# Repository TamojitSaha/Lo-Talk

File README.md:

<h1 align="center">Lo-Talk</h1>

# About

Lo-Talk is an open-hardware ISM band off-grid communicator based on Nordic's NRF51822 and Semtech's LoRa module on SX1278. This device can be helpful in node to node communication and mesh networking over the ISM band and has hardware support for SOS alerts.
The device communication range was tested upto 500mm in an urban area without line of sight and maximum Tx Power 0.3W.

# Schematic

# Layout

# License
The source files are released under  [Creative Commons Attribution-NonCommercial-NoDerivatives 4.0 International License](http://creativecommons.org/licenses/by-nc-nd/4.0/) .

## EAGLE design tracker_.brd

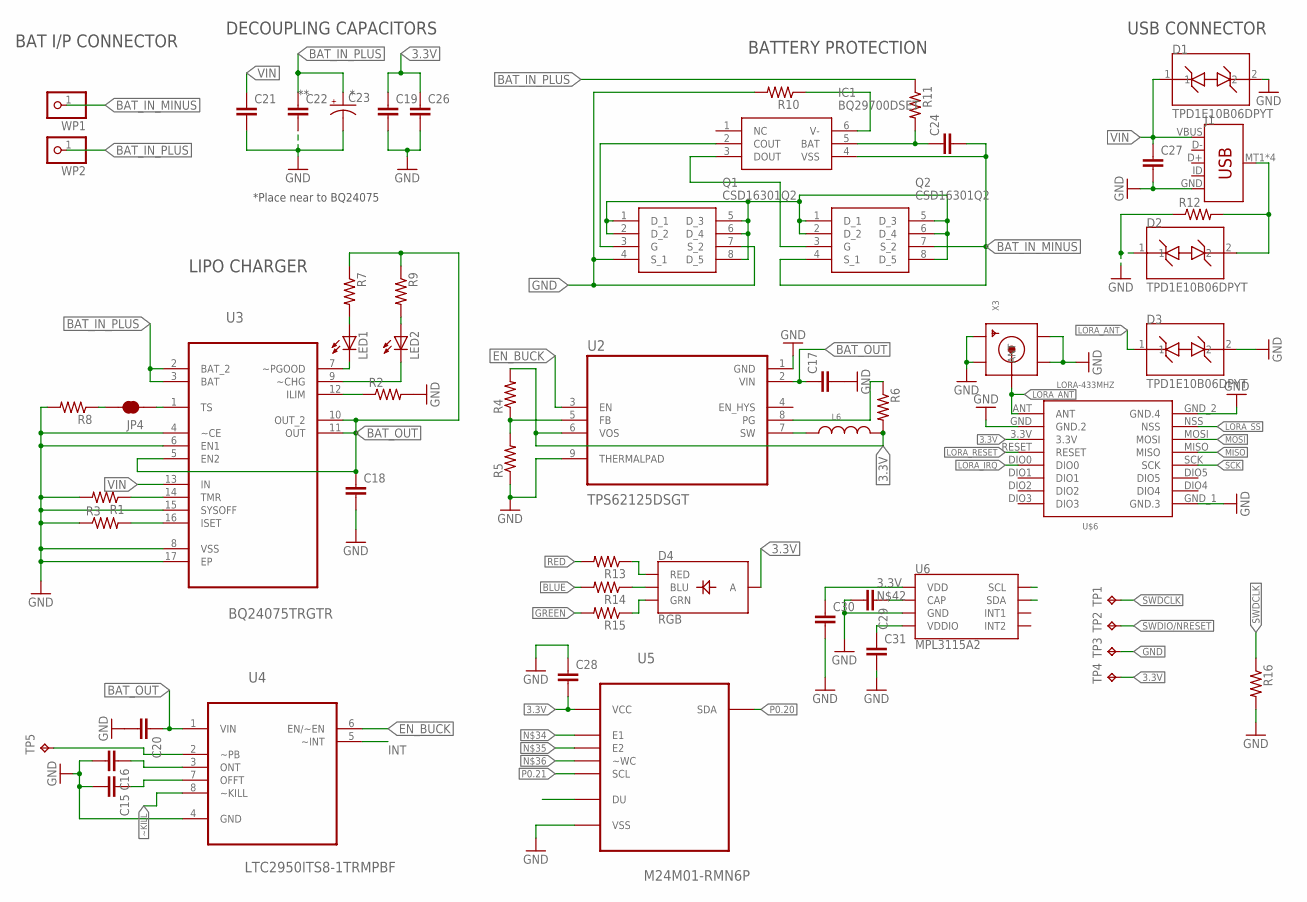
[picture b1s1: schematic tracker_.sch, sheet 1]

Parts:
C15, C16, C17, C18, C20, C21, C28, C29, C30, C31: C-EUC0402; C0402
C19, C24, C26, C27: C-EUC0603; C0603
C22: C-EUC0805K; C0805K
C23: CPOL-USB/3528-21W; B/3528-21W
D1, D2, D3: TPD1E10B06DPYT; DFN100X60X45-2N
D4: RGB; P-LCC-4-3
IC1: BQ29700DSET; SON50P150X150X80-6N
J1: USB_MICRO-B_SMT; USB-MICROB
JP4: JUMPER-SMT_2_NC_TRACE_SILK; SMT-JUMPER_2_NC_TRACE_SILK
L6: WE-GF_1210(M)_744764115; WE-GF_1210
LED1, LED2: LEDCHIPLED_0603; CHIPLED_0603
Q1, Q2: CSD16301Q2
R1, R2, R3, R4, R5, R6, R7, R8, R9, R10, R12, R13, R14, R15, R16: R-US_R0402; R0402
R11: R-US_M0805; M0805
TP1, TP2, TP3, TP4, TP5: TPB1,27; B1,27
U2: TPS62125DSGT; SON50P200X200X80-9N
U3: BQ24075TRGTR; QFN50P300X300X100-17N
U4: LTC2950ITS8-1TRMPBF; SOT65P280X100-8N
U5: M24M01-RMN6P; SOIC127P600X175-8N
U6: MPL3115A2; LGA-8-5X3
U$6: LORA-433MHZ; LORA-RA1-SMD
WP1, WP2: WPAD-1-0805
X3: SMACONNECTOR_EDGE; SMA_EDGELAUNCH

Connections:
3.3V: C19.1, C26.1, C28.2, C30.1, D4.4 (A), L6.2, R4.2, R6.2, TP4.TP, U2.6 (VOS), U5.8 (VCC), U6.1 (VDD), U$6.3.3V; also elsewhere on the board
BAT_IN_MINUS: C24.2, IC1.4 (VSS), Q2.4 (S_1), Q2.7 (S_2), WP1.1
BAT_IN_PLUS: C22.1, C23.+, R11.1, U3.2 (BAT_2), U3.3 (BAT), WP2.1
BAT_OUT: C17.1, C18.1, C20.1, R7.1, R9.1, U2.2 (VIN), U3.5 (EN2), U3.10 (OUT_2), U3.11 (OUT), U4.1 (VIN)
BLUE: R14.2; also elsewhere on the board
DRAIN: Q1.1 (D_1), Q1.2 (D_2), Q1.5 (D_3), Q1.6 (D_4), Q1.8 (D_5), Q2.1 (D_1), Q2.2 (D_2), Q2.5 (D_3), Q2.6 (D_4), Q2.8 (D_5)
EN_BUCK: U2.3 (EN), U4.6 (EN/~EN)
GND: C15.2, C16.2, C17.2, C18.2, C19.2, C20.2, C21.2, C22.2, C23.-, C26.2, C27.2, C28.1, C29.2, C30.2, C31.2, D1.2, D2.1, D3.2, J1.GND, Q1.4 (S_1), Q1.7 (S_2), R1.2, R2.2, R3.1, R5.1, R8.2, R10.2, R12.1, R16.2, TP3.TP, U2.1 (GND), U2.9 (THERMALPAD), U3.4 (~CE), U3.6 (EN1), U3.8 (VSS), U3.15 (SYSOFF), U3.17 (EP), U4.4 (GND), U5.4 (VSS), U6.3 (GND), U$6.GND (GND.2), U$6.GND_1 (GND.3), U$6.GND_2 (GND.4), X3.GND@1 (GND4), X3.GND@2 (GND3), X3.GND@3 (GND2), X3.GND@4 (GND1); also elsewhere on the board
GREEN: R15.2; also elsewhere on the board
INT: U4.5 (~INT)
LORA_ANT: D3.1, U$6.ANT, X3.P (ANT)
LORA_IRQ: U$6.DIO0; also elsewhere on the board
LORA_RESET: U$6.RESET; also elsewhere on the board
LORA_SS: U$6.NSS; also elsewhere on the board
MISO: U$6.MISO; also elsewhere on the board
MOSI: U$6.MOSI; also elsewhere on the board
unnamed: R1.1, U3.14 (TMR)
unnamed: R3.2, U3.16 (ISET)
unnamed: R2.1, U3.12 (ILIM)
unnamed: R4.1, R5.2, U2.5 (FB)
unnamed: LED1.C, U3.7 (~PGOOD)
unnamed: LED2.C, U3.9 (~CHG)
unnamed: LED1.A, R7.2
unnamed: LED2.A, R9.2
unnamed: IC1.2 (COUT), Q1.3 (G)
unnamed: IC1.3 (DOUT), Q2.3 (G)
unnamed: D2.2, J1.MT1 (SHIELD), J1.MT2 (SHIELD), J1.P$1 (SHIELD), J1.P$2 (SHIELD), R12.2
unnamed: D4.1 (RED), R13.1
unnamed: R6.1, U2.8 (PG)
unnamed: JP4.1, U3.1 (TS)
unnamed: D4.3 (BLU), R14.1
unnamed: JP4.2, R8.1
unnamed: IC1.6 (V-), R10.1
unnamed: C16.1, U4.3 (ONT)
unnamed: C15.1, U4.7 (OFFT)
unnamed: C24.1, IC1.5 (BAT), R11.2
unnamed: D4.2 (GRN), R15.1
unnamed: TP5.TP, U4.2 (~PB)
unnamed: C29.1, U6.2 (CAP)
unnamed: C31.1, U6.4 (VDDIO)
P0.20: U5.5 (SDA), U6.7 (SDA); also elsewhere on the board
P0.21: U5.6 (SCL), U6.8 (SCL); also elsewhere on the board
RED: R13.2; also elsewhere on the board
SCK: U$6.SCK; also elsewhere on the board
SW: L6.1, U2.7 (SW)
SWDCLK: R16.1, TP1.TP; also elsewhere on the board
SWDIO/NRESET: TP2.TP; also elsewhere on the board
VIN: C21.1, C27.1, D1.1, J1.VBUS, U3.13 (IN)
~KILL: U4.8 (~KILL); also elsewhere on the board

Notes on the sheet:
BAT I/P CONNECTOR
*Place near to BQ24075
DECOUPLING CAPACITORS
LIPO CHARGER
BATTERY PROTECTION
USB CONNECTOR

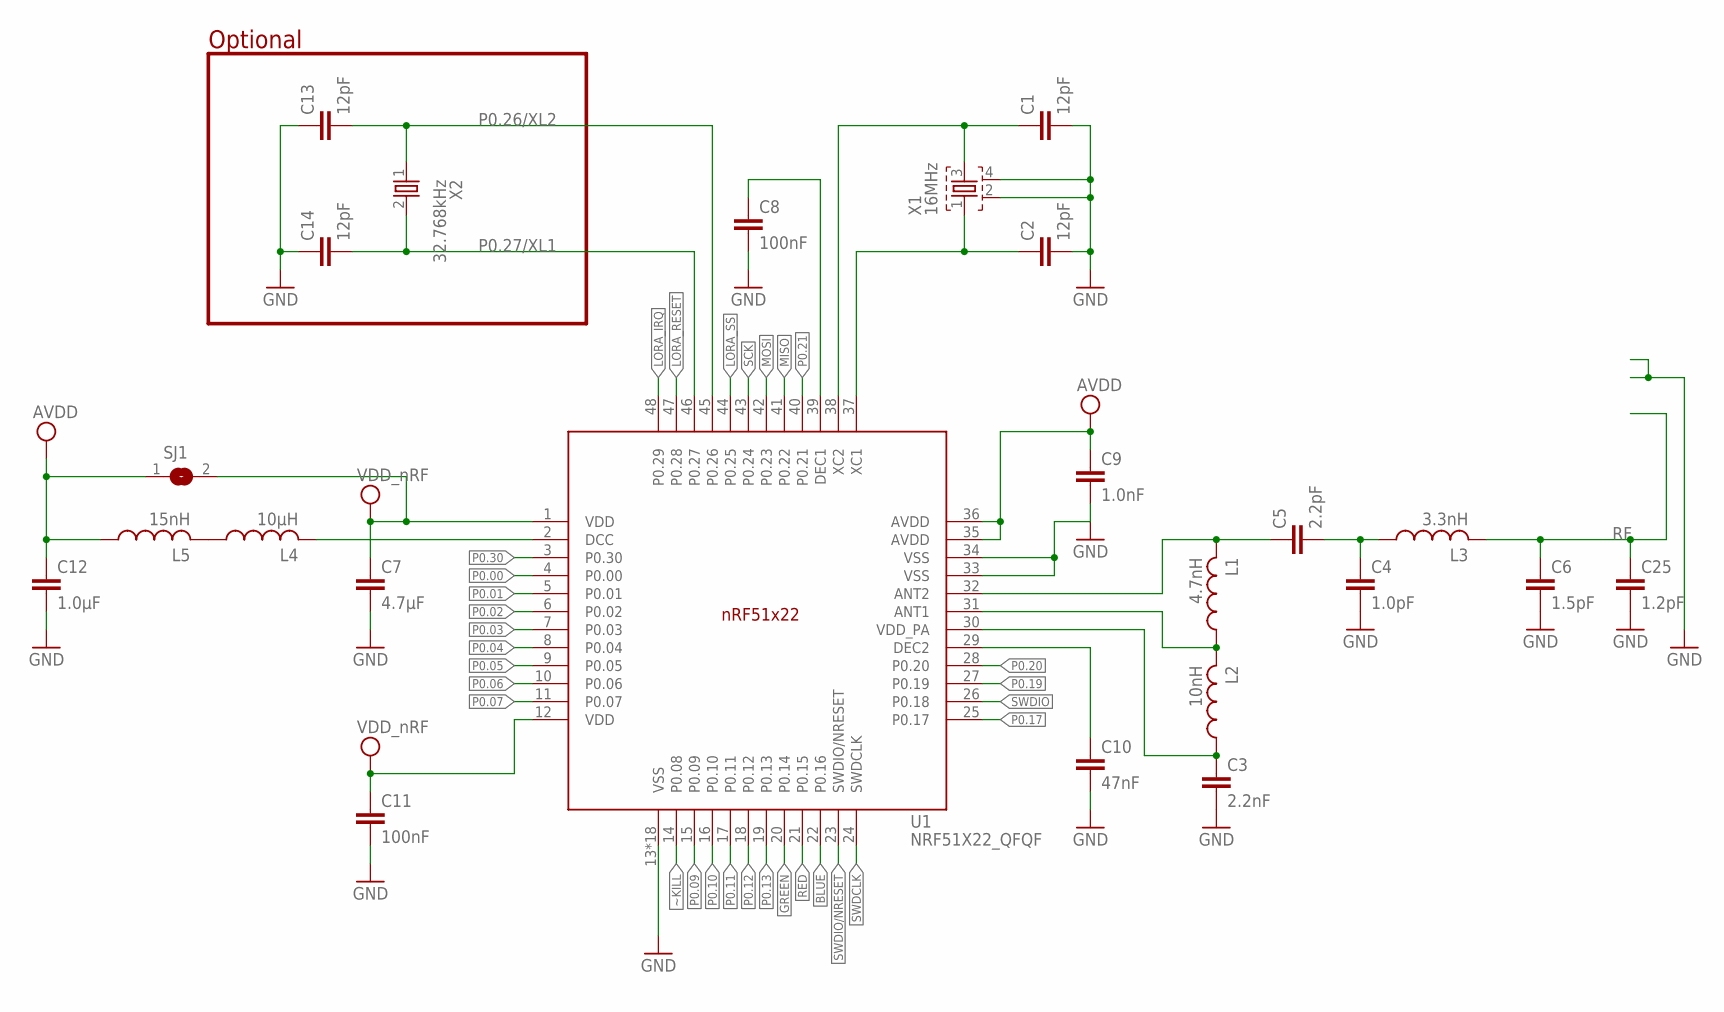
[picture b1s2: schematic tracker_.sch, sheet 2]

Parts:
C1, C2, C13, C14: 12pF; RESC0402_N
C3: 2.2nF; RESC0402_N
C4: 1.0pF; RESC0402_N
C5: 2.2pF; RESC0402_N
C6: 1.5pF; RESC0402_N
C7: 4.7µF; RESC0603_N
C8, C11: 100nF; RESC0402_N
C9: 1.0nF; RESC0402_N
C10: 47nF; RESC0402_N
C12: 1.0µF; RESC0603_N
C25: 1.2pF; RESC0402_N
L1: 4.7nH; RESC0402_N
L2: 10nH; RESC0402_N
L3: 3.3nH; RESC0402_N
L4: 10µH; RESC0603_N
L5: 15nH; RESC0402_N
SJ1: SJ
U1: NRF51X22_QFQF; QFN40P600X600X90-48_N
X1: 16MHz; BT-XTAL_2016_N
X2: 32.768kHz; XTAL_3215_N

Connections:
3.3V: C7.1, C11.1, SJ1.2, U1.1 (VDD), U1.12 (VDD); also elsewhere on the board
AVDD: C9.1, C12.1, L5.1, SJ1.1, U1.35 (AVDD), U1.36 (AVDD)
BLUE: U1.22 (P0.16); also elsewhere on the board
GND: C1.2, C2.2, C3.2, C4.2, C6.2, C7.2, C8.2, C9.2, C10.2, C11.2, C12.2, C13.1, C14.1, C25.2, U1.13 (VSS), U1.33 (VSS), U1.34 (VSS), U1.PAD (VSS), U1.PAD@VIA01 (VSS), U1.PAD@VIA02 (VSS), U1.PAD@VIA03 (VSS), U1.PAD@VIA04 (VSS), U1.PAD@VIA05 (VSS), U1.PAD@VIA06 (VSS), U1.PAD@VIA07 (VSS), U1.PAD@VIA08 (VSS), U1.PAD@VIA09 (VSS), U1.PAD@VIA10 (VSS), U1.PAD@VIA11 (VSS), U1.PAD@VIA12 (VSS), U1.PAD@VIA13 (VSS), U1.PAD@VIA14 (VSS), U1.PAD@VIA15 (VSS), U1.PAD@VIA16 (VSS), X1.2, X1.4; also elsewhere on the board
GREEN: U1.20 (P0.14); also elsewhere on the board
LORA_IRQ: U1.48 (P0.29); also elsewhere on the board
LORA_RESET: U1.47 (P0.28); also elsewhere on the board
LORA_SS: U1.44 (P0.25); also elsewhere on the board
MISO: U1.41 (P0.22); also elsewhere on the board
MOSI: U1.42 (P0.23); also elsewhere on the board
unnamed: L1.1, L2.2, U1.31 (ANT1)
unnamed: L4.1, L5.2
unnamed: C1.1, U1.38 (XC2), X1.3
unnamed: L4.2, U1.2 (DCC)
unnamed: C10.1, U1.29 (DEC2)
unnamed: C8.1, U1.39 (DEC1)
unnamed: C3.1, L2.1, U1.30 (VDD_PA)
unnamed: C5.1, L1.2, U1.32 (ANT2)
unnamed: C4.1, C5.2, L3.1
P0.00: U1.4 (P0.00)
P0.01: U1.5 (P0.01)
P0.02: U1.6 (P0.02)
P0.03: U1.7 (P0.03)
P0.04: U1.8 (P0.04)
P0.05: U1.9 (P0.05)
P0.06: U1.10 (P0.06)
P0.07: U1.11 (P0.07)
P0.09: U1.15 (P0.09)
P0.10: U1.16 (P0.10)
P0.11: U1.17 (P0.11)
P0.12: U1.18 (P0.12)
P0.13: U1.19 (P0.13)
P0.17: U1.25 (P0.17)
P0.19: U1.27 (P0.19)
P0.20: U1.28 (P0.20); also elsewhere on the board
P0.21: U1.40 (P0.21); also elsewhere on the board
P0.26/XL2: C13.2, U1.45 (P0.26), X2.1
P0.27/XL1: C14.2, U1.46 (P0.27), X2.2
P0.30: U1.3 (P0.30)
RED: U1.21 (P0.15); also elsewhere on the board
RF: C6.1, C25.1, L3.2
SCK: U1.43 (P0.24); also elsewhere on the board
SWDCLK: U1.24 (SWDCLK); also elsewhere on the board
SWDIO: U1.26 (P0.18)
SWDIO/NRESET: U1.23 (SWDIO/NRESET); also elsewhere on the board
X1: C2.1, U1.37 (XC1), X1.1
~KILL: U1.14 (P0.08); also elsewhere on the board

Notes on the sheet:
Optional

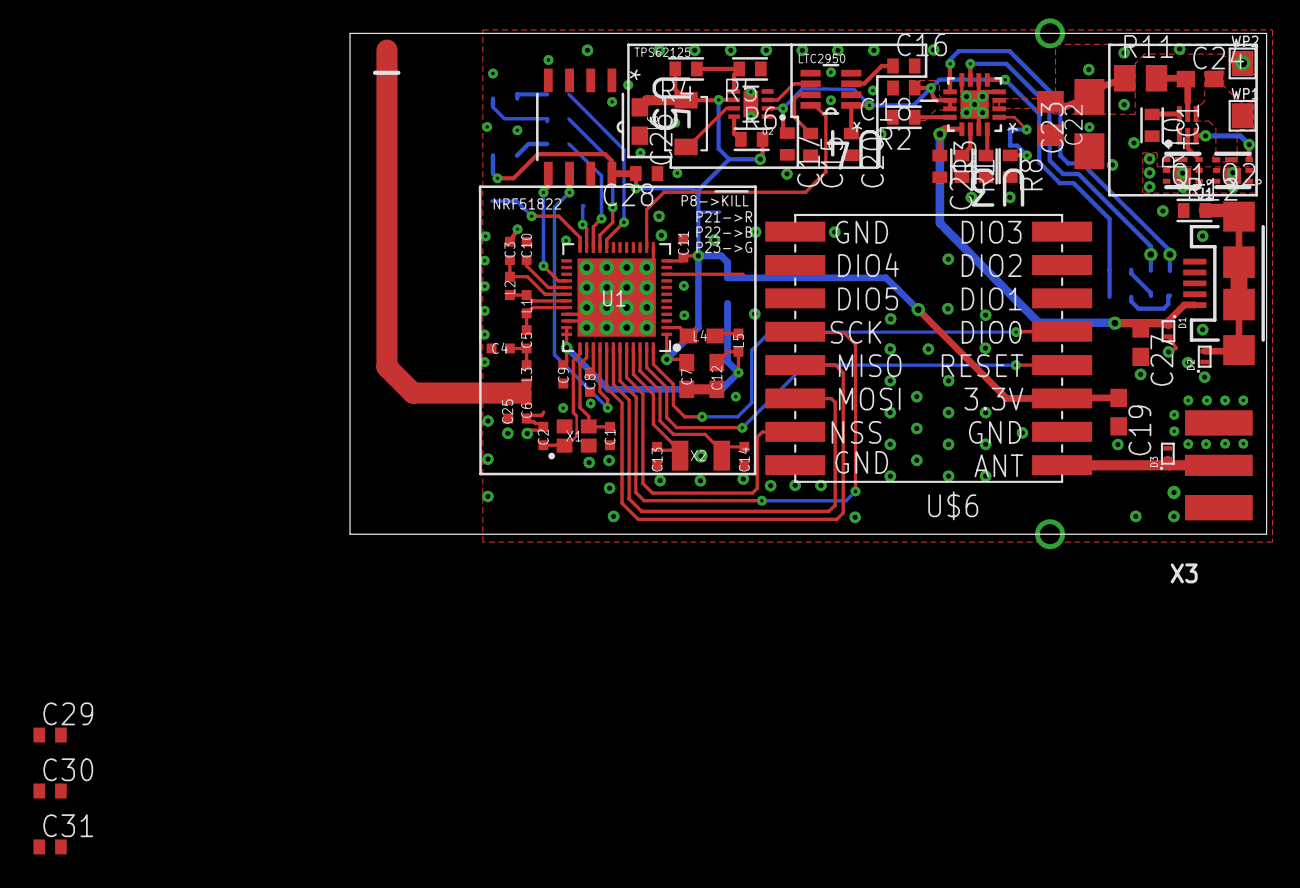
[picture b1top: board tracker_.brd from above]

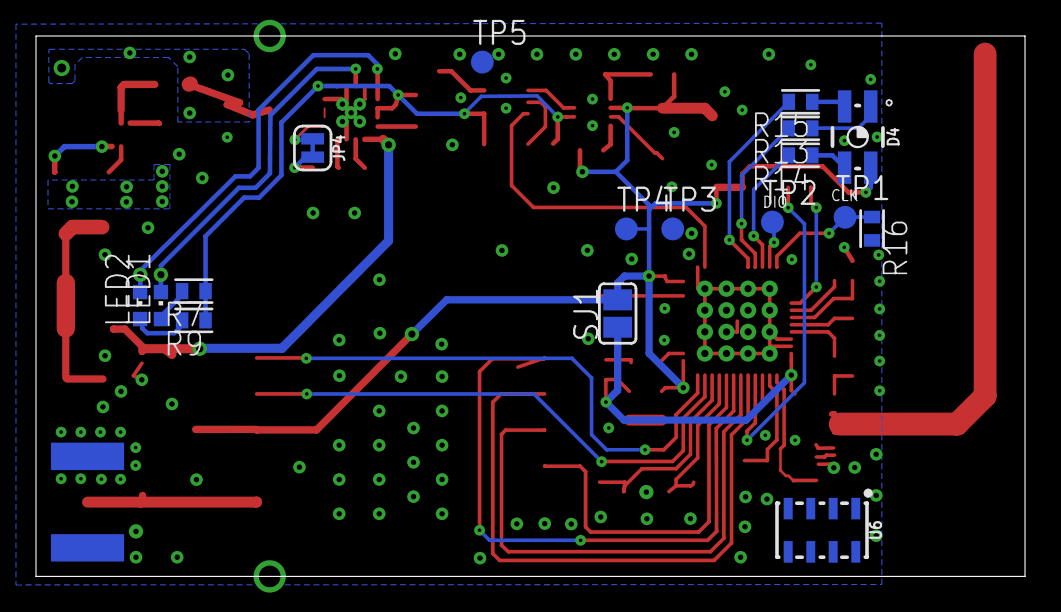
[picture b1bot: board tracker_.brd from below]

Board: 2 copper layers, 54.9 x 30.0 mm, 82 parts (17 on the bottom side), 62 nets.

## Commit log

2018-11-09 Added EagleCAD source files
2018-11-09 Added schematic png
2018-11-09 Added Board layout

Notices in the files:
README.md:
License: CC-BY-NC-ND-4.0
parts and their libraries:
Eagle_AECQ_PRODUCTS: Copyright: Würth Elektronik
SparkFun-Jumpers: Licensing: Creative Commons ShareAlike 4.0 International - https://creativecommons.org/licenses/by-sa/4.0
PatternAgents-ProtoPads: License : http://creativecommons.org/licenses/by-sa/4.0
(Creative Commons 4.0)
